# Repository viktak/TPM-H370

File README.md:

# TPM-H370
TPM 2.0 Module for Gigabyte H370 series motherboards

**WARNING:**
The schematics are correct, tested.
The PCB layout is updated to use the correct connector (v1.1), should be correct, but it is not tested in production!

Further details: https://diy.viktak.com/2022/04/home-made-tpm2-0-module.html.

## License

[Attribution 4.0 International](https://creativecommons.org/licenses/by/4.0/)

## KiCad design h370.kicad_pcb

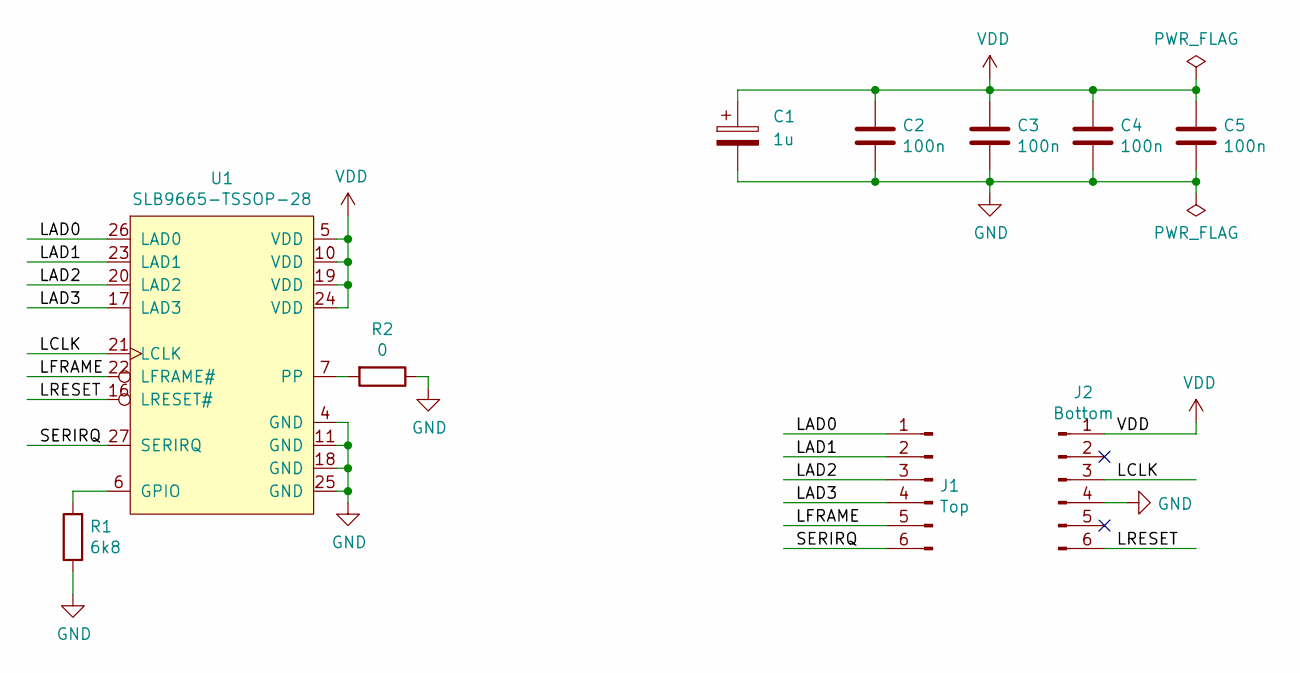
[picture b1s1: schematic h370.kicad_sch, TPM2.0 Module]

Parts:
C1: 1u; CP_EIA-3216-10_Kemet-I
C2, C3, C4, C5: 100n; C_1206_3216Metric
J1: Top; Solder pad connector - 6 pin - 2.0 pitch
J2: Bottom; Solder pad connector - 6 pin - 2.0 pitch
R1: 6k8; R_0805_2012Metric
R2: 0; R_0805_2012Metric
U1: SLB9665-TSSOP-28; TSSOP-28_4.4x9.7mm_P0.65mm

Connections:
/LAD0: J1.1, U1.26 (LAD0)
/LAD1: J1.2, U1.23 (LAD1)
/LAD2: J1.3, U1.20 (LAD2)
/LAD3: J1.4, U1.17 (LAD3)
/LCLK: J2.3, U1.21 (LCLK)
/LFRAME: J1.5, U1.22 (LFRAME#)
/LRESET: J2.6, U1.16 (LRESET#)
/SERIRQ: J1.6, U1.27 (SERIRQ)
GND: C1.2, C2.2, C3.2, C4.2, C5.2, J2.4, R1.1, R2.1, U1.4 (GND), U1.11 (GND), U1.18 (GND), U1.25 (GND)
unnamed: R1.2, U1.6 (GPIO)
unnamed: R2.2, U1.7 (PP)
VDD: C1.1, C2.1, C3.1, C4.1, C5.1, J2.1, U1.5 (VDD), U1.10 (VDD), U1.19 (VDD), U1.24 (VDD)

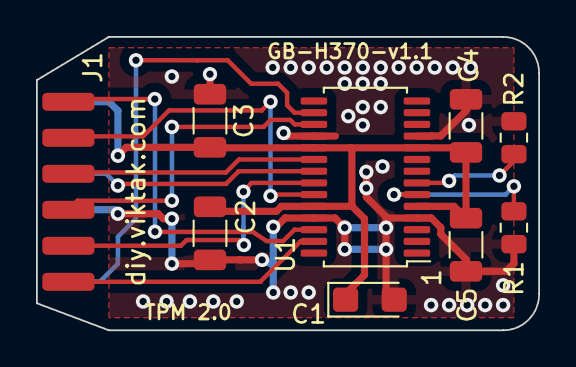
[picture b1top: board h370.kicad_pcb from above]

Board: 2 copper layers, 27.9 x 16.3 mm, 10 parts (1 on the bottom side), 12 nets.

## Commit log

2022-05-04 Initial upload
2022-05-12 License added
